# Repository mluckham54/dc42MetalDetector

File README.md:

arduino Libraries
=================

This repository contains reusable modules, drivers and patches for the Arduino platform. Here is a description of the
projects:

Scheduler
=========
This is a cooperative multi-tasking scheduler for the Arduino. Conventionally, if you need to control and/or monitor
several devices concurrently, then you need to do this in the Arduino loop() function. The code for all the devices is mixed
up, making it difficult to understand and hard to maintain. In contrast, if you use the task scheduler, you can write
the code for each device separately, then just create a task for each device to run its code.

Limitations of the task scheduler:

1. The scheduler is based on a regular tick (normally at 1ms intervals), so any time intervals between things happening
must either be much less that 1ms, or must be multiples of 1ms, or must be specially programmed using one of the
hardware timers.

2. You must write the code for each task so that it executes in much less than 1ms before it returns, so that other
tasks can run. Anything that takes longer must be broke down into smaller steps.

3. You cannot call any library functions that may take more than a millisecond to execute. Library functions that wait
for things to complete need to be rewritten to use the task scheduler instead.

Lcd7920
=======
This is a simple library to drive 128x64 graphic LCDs based on the ST7920 chip in serial mode, thereby using only two
Arduino pins (preferably the MOSI and SCLK pins to get best speed). It is smaller but less comprehensive than U8glib.

PushButton
==========
This is a class to read and debounce a push button. It can be used in conjunction with the task scheduler, or without
if you arrange for your code to call the poll() function at regular intervals.

RotaryEncoder
=============
This is a class to read rotary encoders, allowing for contact bounce and variation in the detent position. It can be
used with or without the task scheduler. To maintain responsiveness, the poll() function must be called at intervals
of 1ms or 2ms.

MetalDetector
=============
A double-D coil metal detector

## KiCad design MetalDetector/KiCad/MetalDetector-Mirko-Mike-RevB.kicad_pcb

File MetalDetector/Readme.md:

**Induction balance metal detector**

This project is an Induction Balance Metal Detector built around Arduino Uno and a 2-line LCD display module driven by I2C.  A piezo buzzer is used to drive an earphone for audio feedback.

The search coil comprises two D-shaped coils fastened on opposite side of a 230mm diameter plastic plate.  The coils are overlapped in the middle to null or minimize the amount of voltage and current induced into the receiver coil when no metal is present.  Position of the overlap is extremely critical, to tune the lowest voltage to an absolute minimum - at which point the Calibration routine can be run.

The form on which the coils are mounted was 3D printed from "DD Coil modifiable by Gabryxx on Thingiverse: https://www.thingiverse.com/thing:5966085".  The original coil was enlarged to 105% to fit the approx 16-cm coils which had already been wound.  In the end, the coil overlap is about 2.5 cm wide and 18 cm long.

The schematic for the detector was taken from Mirko Pavleski's project https://www.hackster.io/mircemk/diy-sensitive-arduino-ib-metal-detector-with-discrimination-b55e9d, modified to replace the LCD display with one I had on hand.  The dc24 project contains KiCad schematics, Mirko's project did not (only a JPG of the circuit).   The circuit was built up on a perfboard and does not seem to suffer from interference, however take care to use grounded shielded wire pairs running from the perfboard to the coils. Leave the shield grounds at the coil end unconnected.

After learning from the comments in Mirko's YouTube video https://www.youtube.com/watch?v=nkSPy0BPTFc&t=5s "DIY sensitive Arduino Induction Balance Metal Detector with Discrimination (15cm to 50 + cm)" came from David Crocker's github project https://github.com/dc42/arduino, it was decided to use his code rather than Mirko's.

The tuning capacitors across the coils should be adjusted such that the LC networks resonate exactly at the frequency generated by the Timer0 PWM output. An oscilloscope is critical to help understand the circuit and the code behaviour, and to tune the coil resonances and phase detection.  The tuning capacitors should be metallised foil types because stable, accurate values are needed. The other capacitors can be ceramic.

The code contains a lot of notes about the discovery process, tuning the coils, understanding how the code works, fixing some issues in the code, and extending it to my liking.

Recently wrapped the non-overlapping part of each coil in grounded aluminium foil (with a gap across that part of the coil that overlaps the other coil).  The coils still can be adjusted to balance.  I didn't notice any change in sensitivity during bench testing.

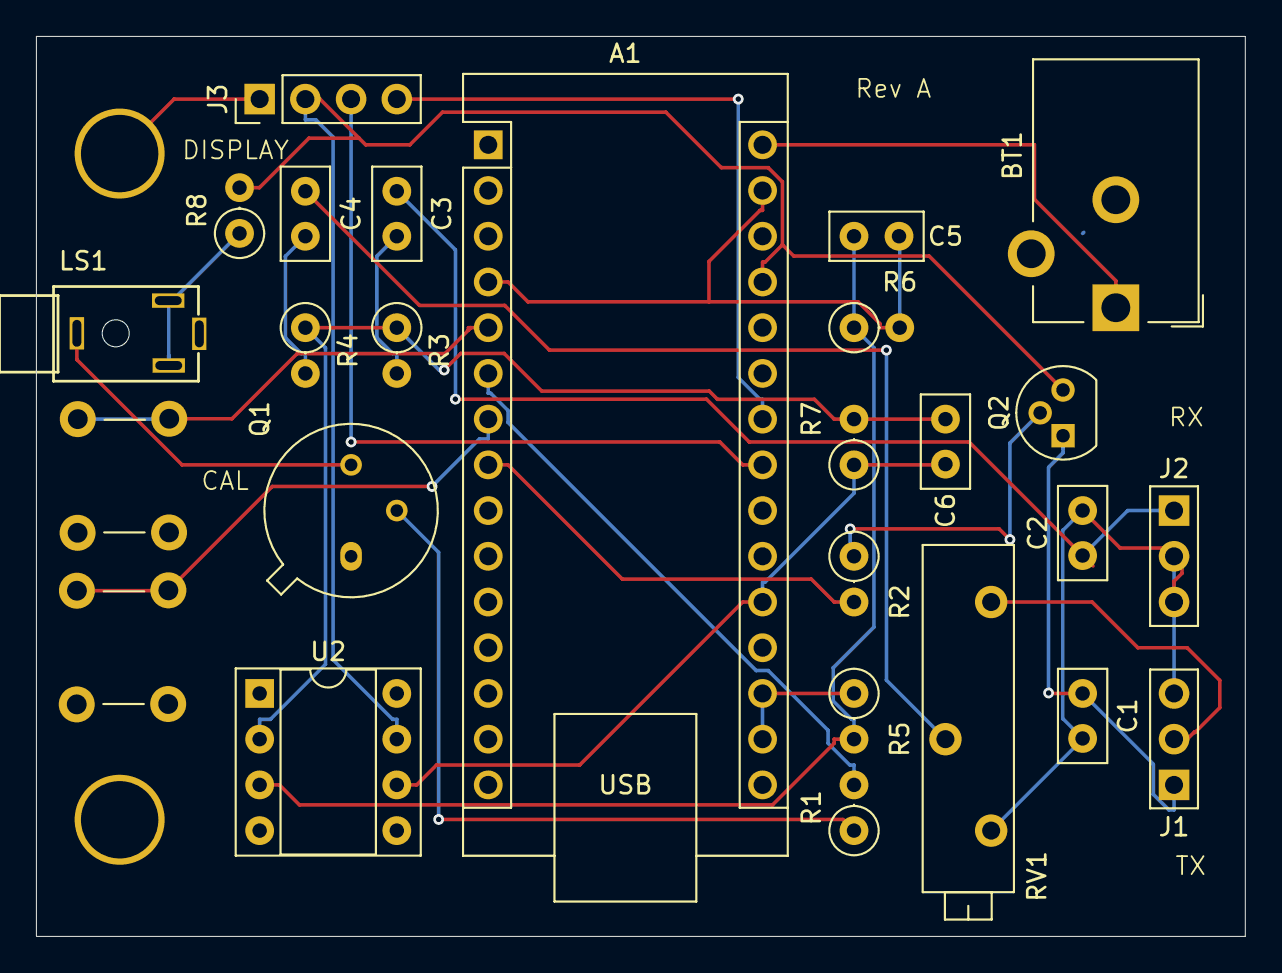
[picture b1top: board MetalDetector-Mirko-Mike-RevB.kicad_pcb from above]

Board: 2 copper layers, 67.2 x 50.0 mm, 28 parts (0 on the bottom side), 23 nets.

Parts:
A1: Arduino_Nano_v3.x; Arduino_Nano
BT1: 2x3.7V Li-Ion; BarrelJack_CUI_PJ-102AH_Horizontal
C1, C2: 305nF; C_Disc_D5.0mm_W2.5mm_P2.50mm
C3: 47nF; C_Disc_D5.0mm_W2.5mm_P2.50mm
C4: 22nF; C_Disc_D5.0mm_W2.5mm_P2.50mm
C5: 100n; C_Disc_D5.0mm_W2.5mm_P2.50mm
C6: 220p; C_Disc_D5.0mm_W2.5mm_P2.50mm
J1, J2: Conn_01x03_Pin; PinHeader_1x03_P2.54mm_Vertical
J3: Display; PinHeader_1x04_P2.54mm_Vertical
LS1: Earphone; CONN_SJ1-2503A
Mounting Hole 1: MountingHole_4.3mm_M4
MountingHole2: MountingHole_4.3mm_M4
Q1: 2N2219; TO-39-3
Q2: 2N4401; TO-92
R1, R2, R3, R4: 1K; R_Axial_DIN0207_L6.3mm_D2.5mm_P2.54mm_Vertical
R5, R6: 100K; R_Axial_DIN0207_L6.3mm_D2.5mm_P2.54mm_Vertical
R7: 47K; R_Axial_DIN0207_L6.3mm_D2.5mm_P2.54mm_Vertical
R8: 100; R_Axial_DIN0207_L6.3mm_D2.5mm_P2.54mm_Vertical
RV1: 100R; Potentiometer_Bourns_3006P_Horizontal
SW1: CAL; SW_PUSH_6mm
SW2: BTN; SW_PUSH_6mm
U2: MCP6281P or MCP6283P or TL081; DIP-8_W7.62mm_Socket

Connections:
GND: A1.4 (GND), A1.29 (GND), BT1.2 (-), C1.2, C2.2, C5.2, J1.3, J2.2, J2.3, J3.1, Mounting Hole 1.1, MountingHole2.1, Q1.1 (E), R6.2, RV1.3, SW1.2, SW2.2, U2.4 (V-)
unnamed: A1.17 (3V3), A1.18 (AREF), R5.1
unnamed: A1.27 (+5V), J3.2, Q2.3 (C), R8.2, U2.7 (V+)
unnamed: A1.20 (A1), C6.2, R7.1, U2.6
unnamed: A1.23 (A4/SDA), J3.3
unnamed: A1.24 (A5/SCL), J3.4
unnamed: A1.5 (D2), SW1.1
unnamed: A1.6 (D3), R1.2
unnamed: A1.7 (D4), SW2.1
unnamed: A1.8 (D5), R2.2
unnamed: C3.2, R3.2
unnamed: C4.1, R4.2
unnamed: C4.2, RV1.2
unnamed: C1.1, J1.1, Q2.1 (E)
unnamed: J1.2, RV1.1
unnamed: C2.1, C3.1, J2.1
unnamed: LS1.T, R8.1
unnamed: Q1.2 (B), R1.1
unnamed: LS1.S, Q1.3 (C)
unnamed: Q2.2 (B), R2.1
unnamed: C5.1, R5.2, R6.1, U2.3 (+)
unnamed: C6.1, R3.1, R4.1, R7.2, U2.2 (-)
PWR: A1.30 (VIN), BT1.1 (+)

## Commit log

2025-02-06 Replaced INO with working code, added photos, schematics, updated the Readme
2025-02-06 add photos, schematics, 3D print files
2025-02-06 add Lissajous scope mp4
2025-02-08 - add coil-amplifier KiCad schematic with working simulation - update README to include MetalDetector project description
2025-02-08 update MetalDetector readme to describe wrapping the coils in foil
2025-02-08 add defined constant for negating the phase
2025-02-11 fix sound generation when amplitude is negative
2025-02-11 Edited the comments about shielding, and mentioned an article using time-delayed measurements to identify the type of metal.
2025-02-11 update comments about further experimentation
2025-02-17 Kicad schematic and PCB work-in-progress
2025-02-18 final PCB version 1, change earphone component on schematic
2025-02-18 ISR can take any consecutive four samples from the available 8
2025-02-22 store string constants in program memory to free up RAM
2025-03-05 - added current limit resistor to headphone circuit - connect output of audio transistor to headphone shield instead of Ring - corrected orientation of power connector on PCB - add notes in the code 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
2025-03-07 added Schematic and PCB Rev B
